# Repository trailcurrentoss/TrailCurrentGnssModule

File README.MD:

# Project Overview
This project is a stand alone GNSS module that utlizes the DFRobot Gravity GNSS receiver. The data that comes in is then formatted and sent over the CAN bus for other modules to use.

Some example use cases are:
-  Digital Clocks
-  Navigation devices
-  Geospatial macros that control devices based on pinned locations

## Enums for GNSS Mode
 -- 1   eGPS              use gps
 -- 2   eBeiDou           use beidou
 -- 3   eGPS_BeiDou       use gps + beidou
 -- 4   eGLONASS          use glonass
 -- 5   eGPS_GLONASS      use gps + glonass
 -- 6   eBeiDou_GLONASS   use beidou +glonass
 -- 7   eGPS_BeiDou_GLONASS use gps + beidou + glonass

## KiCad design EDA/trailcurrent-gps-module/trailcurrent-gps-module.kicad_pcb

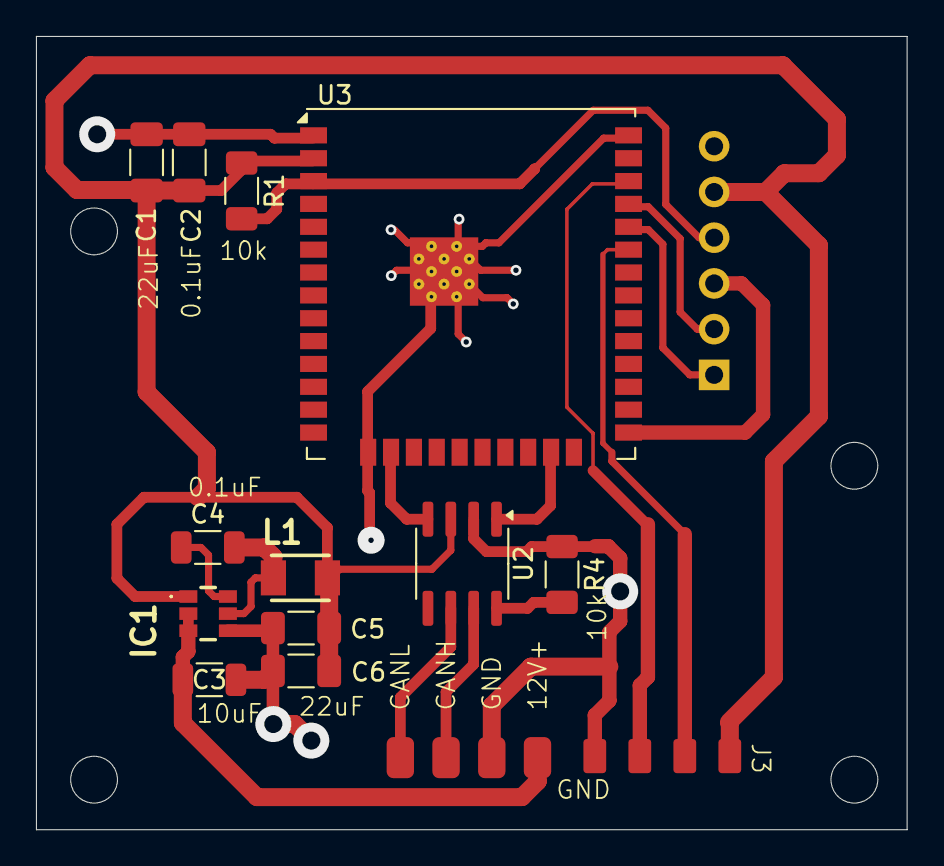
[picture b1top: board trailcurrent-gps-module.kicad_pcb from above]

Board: 2 copper layers, 48.4 x 44.1 mm, 15 parts (1 on the bottom side), 16 nets.

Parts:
C1, C5, C6: 22uF; C_1206_3216Metric_Pad1.33x1.80mm_HandSolder
C2: 0.1uF; C_1206_3216Metric_Pad1.33x1.80mm_HandSolder
C3: 10uF; C_1206_3216Metric
C4: 100nF; C_1206_3216Metric
IC1: AP63203WU-7; AP63203WU7
J1: Conn_01x06; PinHeader_1x06_P2.54mm_Horizontal
J2: Conn_01x04; CAN_PLUS_POWER
J3: Conn_01x04; GenericPad_01x04
L1: NLV32T-3R9J-EF (3.9uH); NLV32T-3R9J-EF
R1, R4: 10k; R_1206_3216Metric_Pad1.30x1.75mm_HandSolder
U2: SN65HVD230; SOIC-8_3.9x4.9mm_P1.27mm
U3: ESP32-WROOM-32U

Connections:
+3.3V: C1.1, C2.1, C5.1, C6.1, IC1.1 (FB), J1.5, J3.4, L1.2, R1.1, U2.3 (VCC), U3.2 (VDD)
+12V: C3.1, IC1.2 (EN), IC1.3 (VIN), J2.1
CANH: J2.3, U2.7 (CANH)
CANL: J2.4, U2.6 (CANL)
CAN_RX: U2.4 (R), U3.16 (IO13)
CAN_TX: U2.1 (D), U3.23 (IO15)
EN: J1.4, R1.2, U3.3 (EN)
ESP32_RX: J1.1, U3.34 (RXD0/IO3)
ESP32_TX: J1.2, U3.35 (TXD0/IO1)
GND: C1.2, C2.2, C3.2, C5.2, C6.2, IC1.4 (GND), J1.6, J2.2, J3.1, R4.1, U2.2 (GND), U3.1 (GND), U3.15 (GND), U3.38 (GND), U3.39 (GND)
IO0: J1.3, U3.25 (IO0)
unnamed: C4.1, IC1.6 (BST)
unnamed: C4.2, IC1.5 (SW), L1.1
unnamed: R4.2, U2.8 (Rs)
SCL: J3.2, U3.36 (IO22)
SDA: J3.3, U3.33 (IO21)

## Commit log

2026-02-12 Initial commit: Clean migration to public Codeberg repository
    This is a fresh start on Codeberg with all security and configuration
    issues addressed:
    Security fixes:
    - Removed all git history (fresh start)
    - No personal paths or credentials exposed
    - All WiFi secrets in .gitignore (using secrets.h.example pattern)
2026-02-12 Removed documentation from project
2026-02-12 Update Codeberg URLs to trailcurrentopensource org
2026-02-14 Fixing license file
2026-02-14 Update docs: replace Codeberg URLs with GitHub references
2026-02-21 Wifi and OTA changes
2026-02-21 Converted to reusable libraries for CAN and OTA
2026-02-23 Add trailcurrent.com link to README
2026-03-15 Renamed repo
2026-03-15 Updating documentation
